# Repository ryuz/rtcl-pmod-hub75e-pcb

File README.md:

# HUB-75E LEDパネルを PMOD １個で駆動する基板

## 概要

HUB75E 形式の LED パネルを PMOD １個で駆動するための変換基板です。

Sipeed さんの [PMOD_HUB75E](https://wiki.sipeed.com/hardware/en/tang/tang-PMOD/FPGA_PMOD.html) だと PMOD コネクタが２個必要で、KV260 などのように PMOD コネクタが１個しかない FPGA ボードでは利用できません。

そこで PMOD 一個からデュアルエッジでデータを出して 64x64 の LED パネルを駆動するための基板を設計しました。

## 変換基板のイメージ

下記のような変換基板です。

PMOD コネクタ一個から HUB-75E LED パネルを駆動します。

## 各種データ

Ver1 の 回路図は[こちら](rtcl-pmod-hub75e-v1.pdf)です。

[KiCAD](https://www.kicad.org/) version 10.0.1 で設計しております。

[JLCPCB](https://jlcpcb.com/) さんの4層基板で製造を想定しております。

手元での試作は JLCPCB さんの PCBA で行っており、各自で製造される場合は必要に応じて部品を選定ください。

## 動作テスト

下記のプロジェクトなどで動作テストを行っております。

- https://github.com/ryuz/rtcl-designs/tree/develop/projects/kv260/kv260_rtcl_hub75e_sample

LED パネルの表示確認や各種パラメータの調整を行っております。

## 免責事項

本設計データは、研究開発用の試作実験に用するものであり、利用に際して発生した如何なる損害も作者は補償いたしませんので予めご了承ください。

## ライセンス(License)

本設計データは、[クリエイティブ・コモンズ 表示-非営利 4.0 国際 ライセンス](https://creativecommons.org/licenses/by-nc/4.0/deed.ja)の下で提供されています。

製造した本基板の販売や配布を行わない限りは、趣味や研究開発用途でご自由にお使いいただく事が出来ます。
また、商用に製造販売を希望される場合は、別途ライセンス契約を作者までご相談ください。

## 作者情報

渕上 竜司(Ryuji Fuchikami)
[リアルタイムコンピューティング研究所](https://rtc-lab.com/)

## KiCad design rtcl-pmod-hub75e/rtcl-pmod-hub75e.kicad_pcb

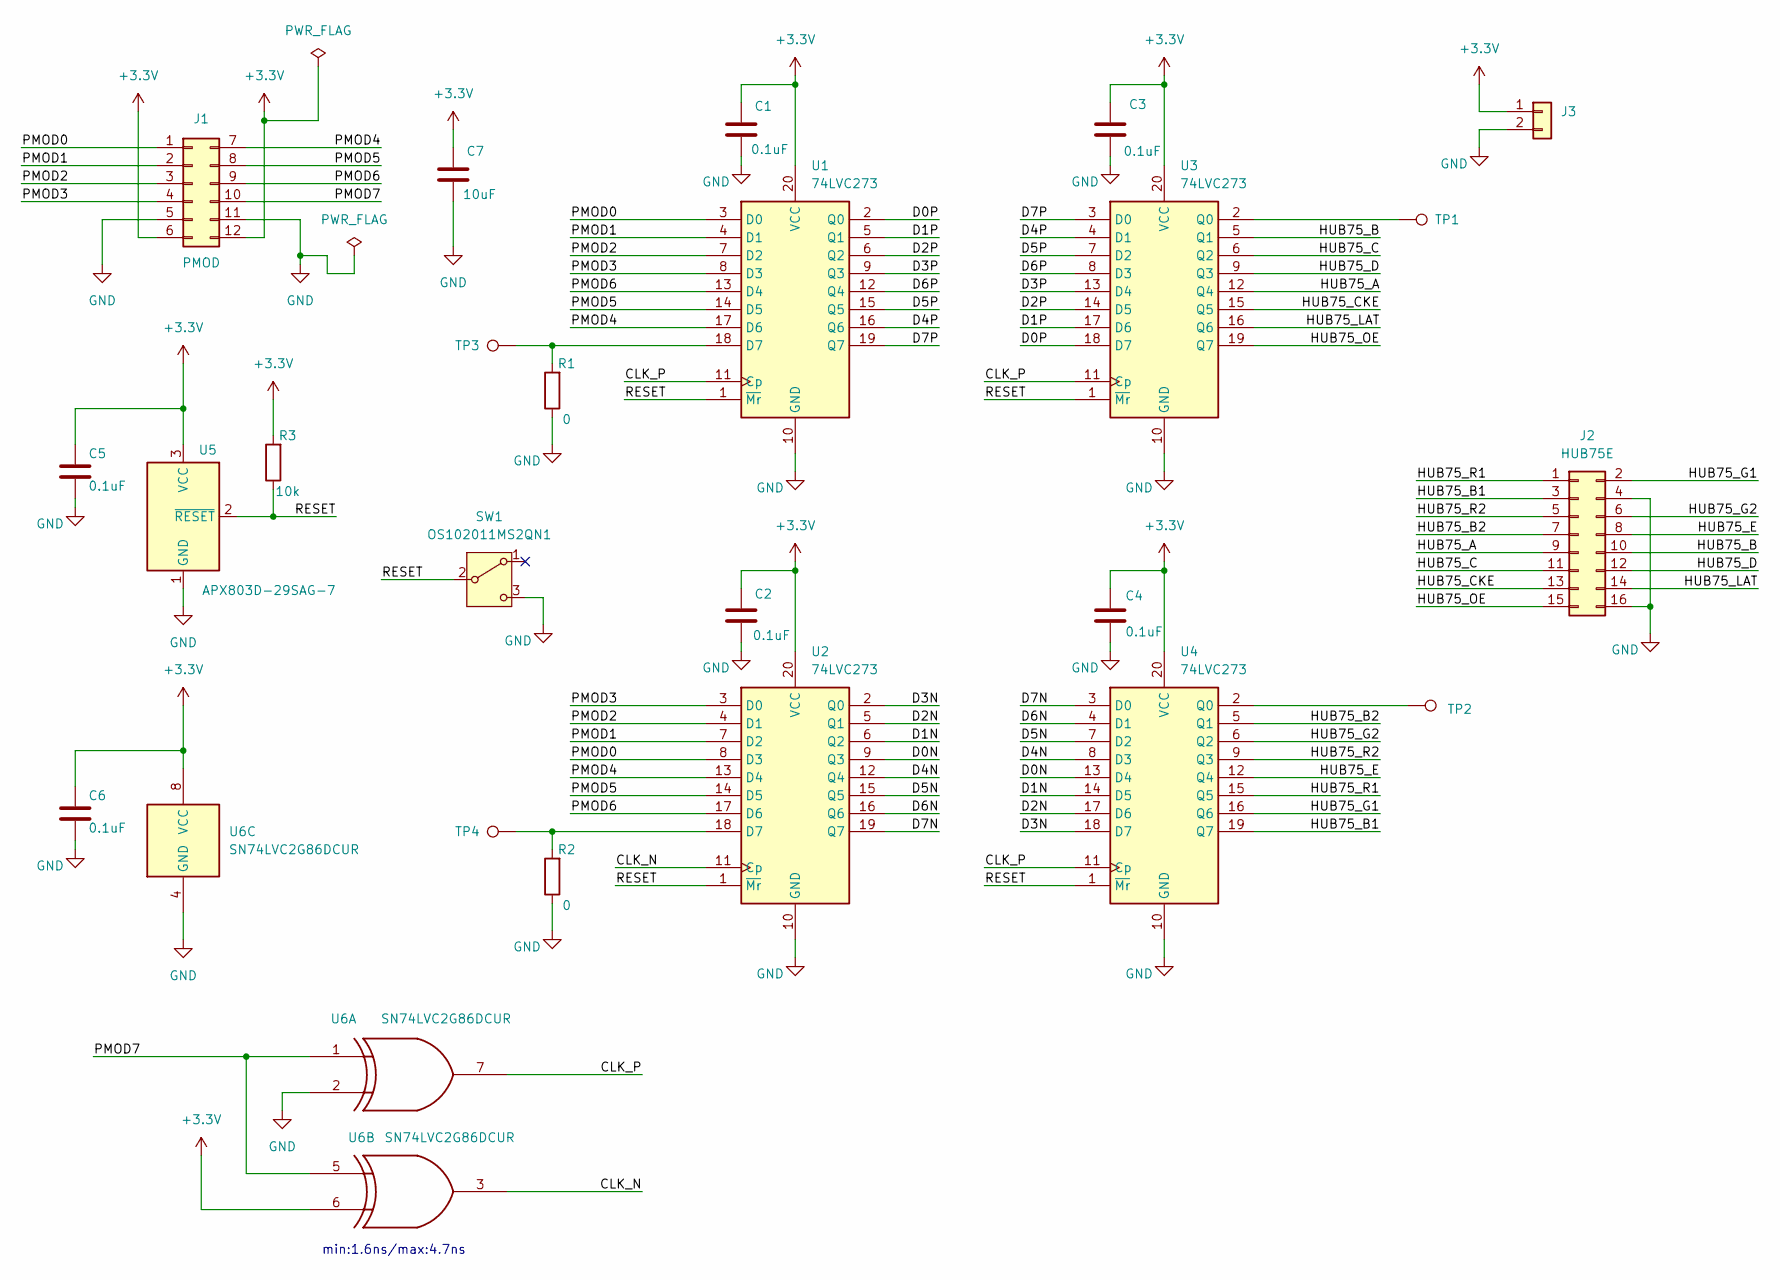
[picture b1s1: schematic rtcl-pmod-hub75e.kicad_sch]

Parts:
C1, C2, C3, C4, C5, C6: 0.1uF; C_0603_1608Metric
C7: 10uF; C_0603_1608Metric
J1: PMOD; PH_02x06_2.54mm; LCSC C124371
J2: HUB75E; PH_02x08_2.54mm; LCSC C7430313
J3: Conn_01x02; PinHeader_1x02_P2.54mm_Vertical
R1, R2: 0; R_0603_1608Metric
R3: 10k; R_0603_1608Metric
SW1: OS102011MS2QN1; SW_OS102011MS2QN1; LCSC C221829
TP1, TP2, TP3, TP4: TestPoint; TestPoint_Pad_D1.0mm
U1, U2, U3, U4: 74LVC273; TSSOP-20_4.4x6.5mm_P0.65mm; LCSC C456144
U5: APX803D-29SAG-7; SOT-23-3; LCSC C460555
U6: SN74LVC2G86DCUR; VSSOP-8_2.3x2mm_P0.5mm; LCSC C507252

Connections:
+3.3V: C1.1, C2.1, C3.1, C4.1, C5.1, C6.1, C7.1, J1.6, J1.12, J3.1, R3.2, U1.20 (VCC), U2.20 (VCC), U3.20 (VCC), U4.20 (VCC), U5.3 (VCC), U6.6, U6.8 (VCC)
/CLK_N: U2.11 (Cp), U6.3
/CLK_P: U1.11 (Cp), U3.11 (Cp), U4.11 (Cp), U6.7
/D0N: U2.9 (Q3), U4.13 (D4)
/D0P: U1.2 (Q0), U3.18 (D7)
/D1N: U2.6 (Q2), U4.14 (D5)
/D1P: U1.5 (Q1), U3.17 (D6)
/D2N: U2.5 (Q1), U4.17 (D6)
/D2P: U1.6 (Q2), U3.14 (D5)
/D3N: U2.2 (Q0), U4.18 (D7)
/D3P: U1.9 (Q3), U3.13 (D4)
/D4N: U2.12 (Q4), U4.8 (D3)
/D4P: U1.16 (Q6), U3.4 (D1)
/D5N: U2.15 (Q5), U4.7 (D2)
/D5P: U1.15 (Q5), U3.7 (D2)
/D6N: U2.16 (Q6), U4.4 (D1)
/D6P: U1.12 (Q4), U3.8 (D3)
/D7N: U2.19 (Q7), U4.3 (D0)
/D7P: U1.19 (Q7), U3.3 (D0)
/HUB75_A: J2.9, U3.12 (Q4)
/HUB75_B: J2.10, U3.5 (Q1)
/HUB75_B1: J2.3, U4.19 (Q7)
/HUB75_B2: J2.7, U4.5 (Q1)
/HUB75_C: J2.11, U3.6 (Q2)
/HUB75_CKE: J2.13, U3.15 (Q5)
/HUB75_D: J2.12, U3.9 (Q3)
/HUB75_E: J2.8, U4.12 (Q4)
/HUB75_G1: J2.2, U4.16 (Q6)
/HUB75_G2: J2.6, U4.6 (Q2)
/HUB75_LAT: J2.14, U3.16 (Q6)
/HUB75_OE: J2.15, U3.19 (Q7)
/HUB75_R1: J2.1, U4.15 (Q5)
/HUB75_R2: J2.5, U4.9 (Q3)
/PMOD0: J1.1, U1.3 (D0), U2.8 (D3)
/PMOD1: J1.2, U1.4 (D1), U2.7 (D2)
/PMOD2: J1.3, U1.7 (D2), U2.4 (D1)
/PMOD3: J1.4, U1.8 (D3), U2.3 (D0)
/PMOD4: J1.7, U1.17 (D6), U2.13 (D4)
/PMOD5: J1.8, U1.14 (D5), U2.14 (D5)
/PMOD6: J1.9, U1.13 (D4), U2.17 (D6)
/PMOD7: J1.10, U6.1, U6.5
/RESET: R3.1, SW1.2 (B), U1.1 (~Mr), U2.1 (~Mr), U3.1 (~Mr), U4.1 (~Mr), U5.2 (~RESET)
GND: C1.2, C2.2, C3.2, C4.2, C5.2, C6.2, C7.2, J1.5, J1.11, J2.4, J2.16, J3.2, R1.1, R2.1, SW1.3 (C), U1.10 (GND), U2.10 (GND), U3.10 (GND), U4.10 (GND), U5.1 (GND), U6.2, U6.4 (GND)
unnamed: R1.2, TP3.1 (1_1), U1.18 (D7)
unnamed: R2.2, TP4.1 (1_1), U2.18 (D7)
unnamed: TP1.1 (1_1), U3.2 (Q0)
unnamed: TP2.1 (1_1), U4.2 (Q0)

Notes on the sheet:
min:1.6ns/max:4.7ns

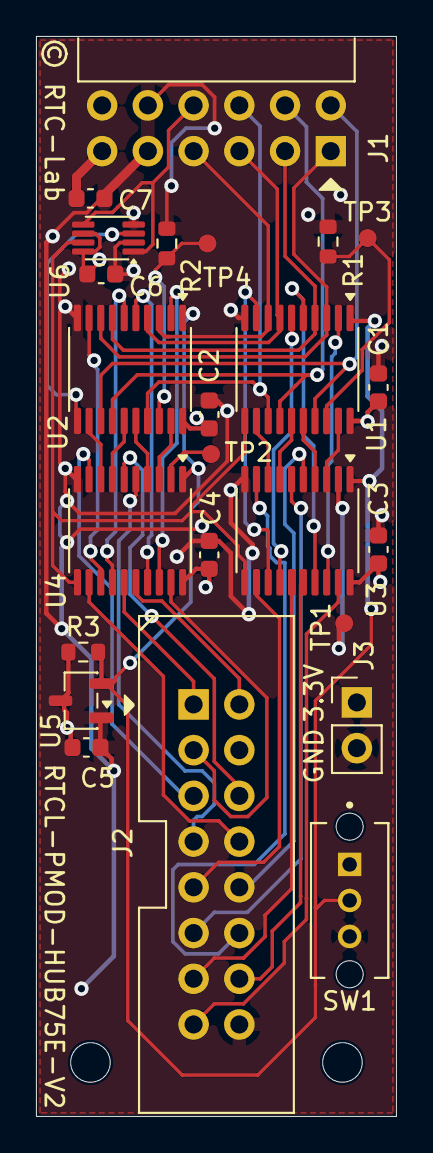
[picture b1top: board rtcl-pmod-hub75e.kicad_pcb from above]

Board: 4 copper layers, 20.0 x 60.0 mm, 24 parts (0 on the bottom side), 47 nets.

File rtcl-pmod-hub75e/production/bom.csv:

Designator,Footprint,Quantity,Value,LCSC Part #
"C1, C2, C3, C4, C5, C6",0603,6,0.1uF,
C7,0603,1,10uF,
J1,PH_02x06_2.54mm,1,PMOD,C124371
J2,PH_02x08_2.54mm,1,HUB75E,C7430313
J3,PinHeader_1x02_P2.54mm_Vertical,1,Conn_01x02,
"R1, R2",0603,2,0,
R3,0603,1,10k,
SW1,SW_OS102011MS2QN1,1,OS102011MS2QN1,C221829
"TP1, TP2, TP3, TP4",TestPoint_Pad_D1.0mm,4,TestPoint,
"U1, U2, U3, U4",TSSOP-20_4.4x6.5mm_P0.65mm,4,74LVC273,C456144
U5,SOT-23-3,1,APX803D-29SAG-7,C460555
U6,VSSOP-8_2.3x2mm_P0.5mm,1,SN74LVC2G86DCUR,C507252

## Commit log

2026-05-04 1st commit
2026-05-04 Update .gitignore and modify schematic for power symbols and designators
2026-05-05 Add footprints for PH_02x06_2.54mm and PH_02x08_2.54mm headers; update existing schematic properties
2026-05-05 Refactor PH_02x06_2.54mm.kicad_mod: Update properties, adjust pin positions, and modify silk screen lines for improved clarity and accuracy
2026-05-05 Update design rules and footprint for PH_02x08_2.54mm header
    - Modified differential pair dimensions and DRC exclusions in the project configuration.
    - Adjusted various design rule checks (DRC) to change warnings to errors or ignore them as necessary.
    - Updated minimum clearance and hole clearance values for better manufacturability.
    - Changed track widths and via dimensions to accommodate new design requirements.
    - Revised the footprint for PH_02x08_2.54mm header, including repositioning properties and updating UUIDs for pads and lines.
    - Ensured all pads are correctly placed and sized for optimal performance.
2026-05-05 Refactor code structure for improved readability and maintainability
2026-05-05 Update PCB design parameters and wire connections in the rtcl-pmod-hub75e project
    - Changed active layer from 0 to 2 in the project settings.
    - Cleared used designators in the project file for better clarity.
    - Adjusted multiple wire connection points in the schematic to correct coordinates for improved layout.
    - Updated label positions for various components to reflect new wire connections and ensure proper alignment.
2026-05-05 Update PCB layout settings: change active layer to 0 and adjust selection filter options
2026-05-05 Update active layer and adjust wire positions in schematic
    - Changed active layer from 0 to 2 in the PCB layout.
    - Adjusted multiple wire coordinates in the schematic to correct alignment.
    - Updated label positions for various components to ensure proper placement.
    - Modified test point coordinates for better alignment with the design.
2026-05-05 Update selection filter and zone display mode in KiCad project file
    - Changed selection filter for footprints from true to false
    - Updated zone display mode from 0 to 1
2026-05-05 Disable vias visibility in the PCB layout for the rtcl-pmod-hub75e project
2026-05-05 Update selection filter settings in rtcl-pmod-hub75e.kicad_prl to enable footprints and vias
2026-05-05 Update PCB and schematic files for rtcl-pmod-hub75e
    - Changed active layer from 2 to 5 in the PCB layout.
    - Modified visibility settings for text, tracks, and vias in the PCB layout.
    - Updated visible layers in the PCB layout.
    - Changed footprint references from "TestPoint" to "rtcl-pmod-hub75e" in the schematic.
    - Updated UUIDs for various elements in the PH_02x08_2.54mm footprint.
    - Added new footprint for TestPoint_Pad_D1.0mm.
2026-05-05 Update active layer and selection filter settings in KiCad project files
2026-05-05 Update active layer and selection filter settings in PCB layout
    - Changed active layer from 0 to 4 for improved visibility.
    - Modified selection filter to disable dimensions, footprints, graphics, keepouts, other items, pads, text, and zones for a cleaner interface.
2026-05-05 Update KiCad project files and component model for PH_02x06_2.54mm
    - Changed active layer in rtcl-pmod-hub75e.kicad_prl from 4 to 0.
    - Updated UUIDs for various properties and elements in PH_02x06_2.54mm.kicad_mod.
    - Added embedded model for PH_02x06_2.54mm component with specified offset, scale, and rotation.
2026-05-05 Refactor KiCad project files: remove obsolete footprint PH_02x06_2.54mm, update PCB layout and schematic, and enable footprint visibility in selection filter settings.
2026-05-05 Add LCSC properties for components in schematic
2026-05-05 Add production files including BOM, designators, netlist, positions, and PCB layout updates
    - Created BOM file with component details and LCSC part numbers.
    - Added designators for all components in the design.
    - Generated netlist for IPC format.
    - Included positions for components with coordinates and rotations.
    - Updated PCB layout with new component properties and visibility settings.
    - Adjusted solder mask clearance in project settings.
2026-05-05 Update PCB and PRL files: adjust capacitor position and modify active layer settings
2026-05-15 Add README and image for HUB-75E LED panel PMOD board
2026-05-31 Add new footprints for SPDT switch and OS102011MS2QN1 switch
    - Created a new footprint for SPDT switch (SPDT_OS102011_CNK) with detailed pad and silk layer definitions.
    - Added a new footprint for OS102011MS2QN1 switch, including properties, pads, and 3D model reference.
2026-05-31 Update active layer in rtcl-pmod-hub75e.kicad_prl from 5 to 1
2026-05-31 Update README and add LCSC part number for OS102011MS2QN1 switch

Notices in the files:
rtcl-pmod-hub75e/rtcl-pmod-hub75e.kicad_pcb:
© RTC-Lab
